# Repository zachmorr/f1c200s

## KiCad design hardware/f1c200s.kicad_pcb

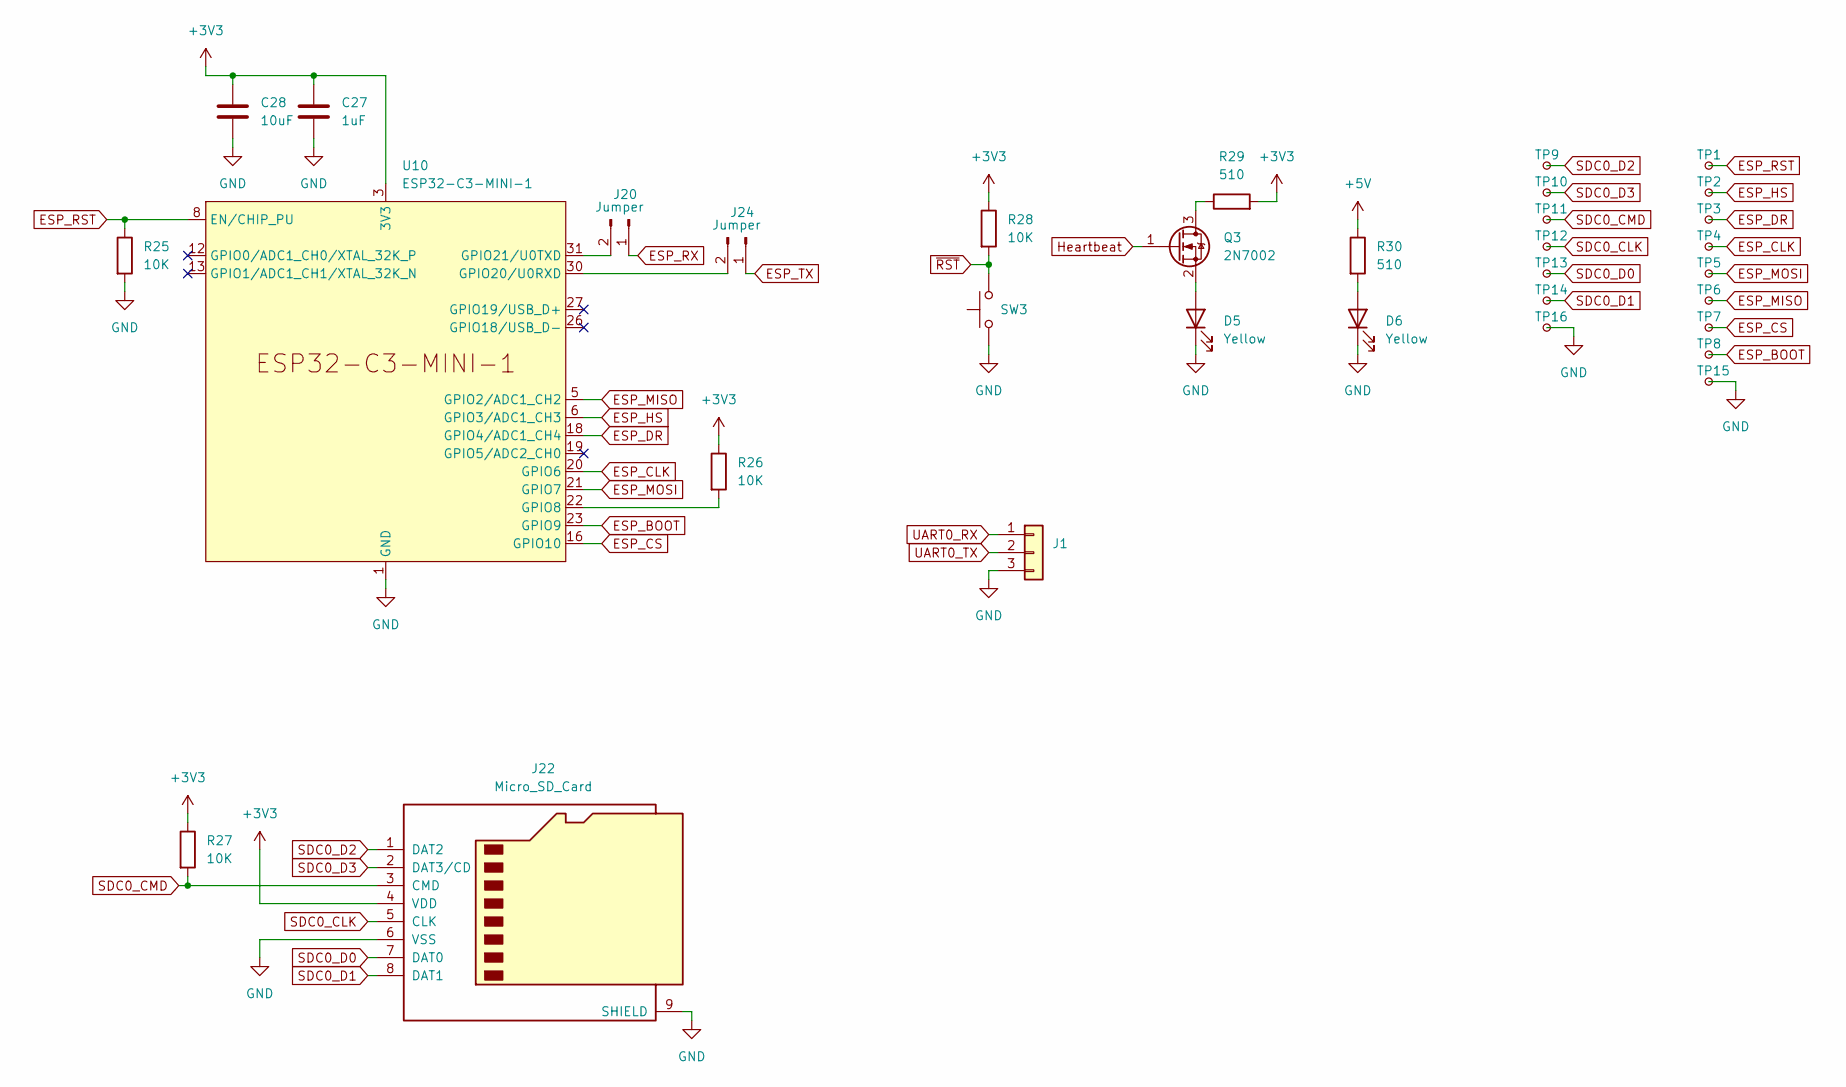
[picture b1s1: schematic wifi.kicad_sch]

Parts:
C27: 1uF; C_0402_1005Metric; LCSC C52923
C28: 10uF; C_0402_1005Metric; LCSC C15525
D5, D6: Yellow; LED_0603_1608Metric; LCSC C72038
J1: Conn_01x03; PinHeader_1x03_P2.54mm_Vertical
J20, J24: Jumper; PinHeader_1x02_P2.54mm_Vertical
J22: Micro_SD_Card; microSD_HC_Molex_104031-0811; LCSC C585350
Q3: 2N7002; SOT-23; LCSC C8545
R25, R26, R27, R28: 10K; R_0603_1608Metric; LCSC C25804
R29, R30: 510; R_0603_1608Metric; LCSC C23193
SW3: SW_Push; SW_Push_1P1T_XKB_TS-1187A; LCSC C318884
TP1, TP2, TP3, TP4, TP5, TP6, TP7, TP8, TP9, TP10, TP11, TP12, TP13, TP14, TP15, TP16: TestPoint_Small; TestPoint_Pad_D1.0mm
U10: ESP32-C3-MINI-1

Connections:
+3V3: C27.1, C28.1, J22.4 (VDD), R26.1, R27.1, R28.1, R29.2, U10.3 (3V3); also elsewhere on the board
+5V: R30.1; also elsewhere on the board
ESP_BOOT: TP8.1, U10.23 (GPIO9); also elsewhere on the board
ESP_CLK: TP4.1, U10.20 (GPIO6); also elsewhere on the board
ESP_CS: TP7.1, U10.16 (GPIO10); also elsewhere on the board
ESP_DR: TP3.1, U10.18 (GPIO4/ADC1_CH4); also elsewhere on the board
ESP_HS: TP2.1, U10.6 (GPIO3/ADC1_CH3); also elsewhere on the board
ESP_MISO: TP6.1, U10.5 (GPIO2/ADC1_CH2); also elsewhere on the board
ESP_MOSI: TP5.1, U10.21 (GPIO7); also elsewhere on the board
ESP_RST: R25.1, TP1.1, U10.8 (EN/CHIP_PU); also elsewhere on the board
ESP_RX: J20.1; also elsewhere on the board
ESP_TX: J24.1; also elsewhere on the board
GND: C27.2, C28.2, D5.1 (K), D6.1 (K), J1.3, J22.6 (VSS), J22.9 (SHIELD), R25.2, SW3.1, TP15.1, TP16.1, U10.1 (GND), U10.2 (GND), U10.11 (GND), U10.14 (GND), U10.36 (GND), U10.37 (GND), U10.38 (GND), U10.39 (GND), U10.40 (GND), U10.41 (GND), U10.42 (GND), U10.43 (GND), U10.44 (GND), U10.45 (GND), U10.46 (GND), U10.47 (GND), U10.48 (GND), U10.49 (GND), U10.50 (GND), U10.51 (GND), U10.52 (GND), U10.53 (GND); also elsewhere on the board
Heartbeat: Q3.1 (G)
unnamed: D5.2 (A), Q3.2 (S)
unnamed: D6.2 (A), R30.2
unnamed: J20.2, U10.31 (GPIO21/U0TXD)
unnamed: J24.2, U10.30 (GPIO20/U0RXD)
unnamed: Q3.3 (D), R29.1
unnamed: R26.2, U10.22 (GPIO8)
SDC0_CLK: J22.5 (CLK), TP12.1; also elsewhere on the board
SDC0_CMD: J22.3 (CMD), R27.2, TP11.1; also elsewhere on the board
SDC0_D0: J22.7 (DAT0), TP13.1; also elsewhere on the board
SDC0_D1: J22.8 (DAT1), TP14.1; also elsewhere on the board
SDC0_D2: J22.1 (DAT2), TP9.1; also elsewhere on the board
SDC0_D3: J22.2 (DAT3/CD), TP10.1; also elsewhere on the board
UART0_RX: J1.1; also elsewhere on the board
UART0_TX: J1.2; also elsewhere on the board
~RST: R28.2, SW3.2; also elsewhere on the board

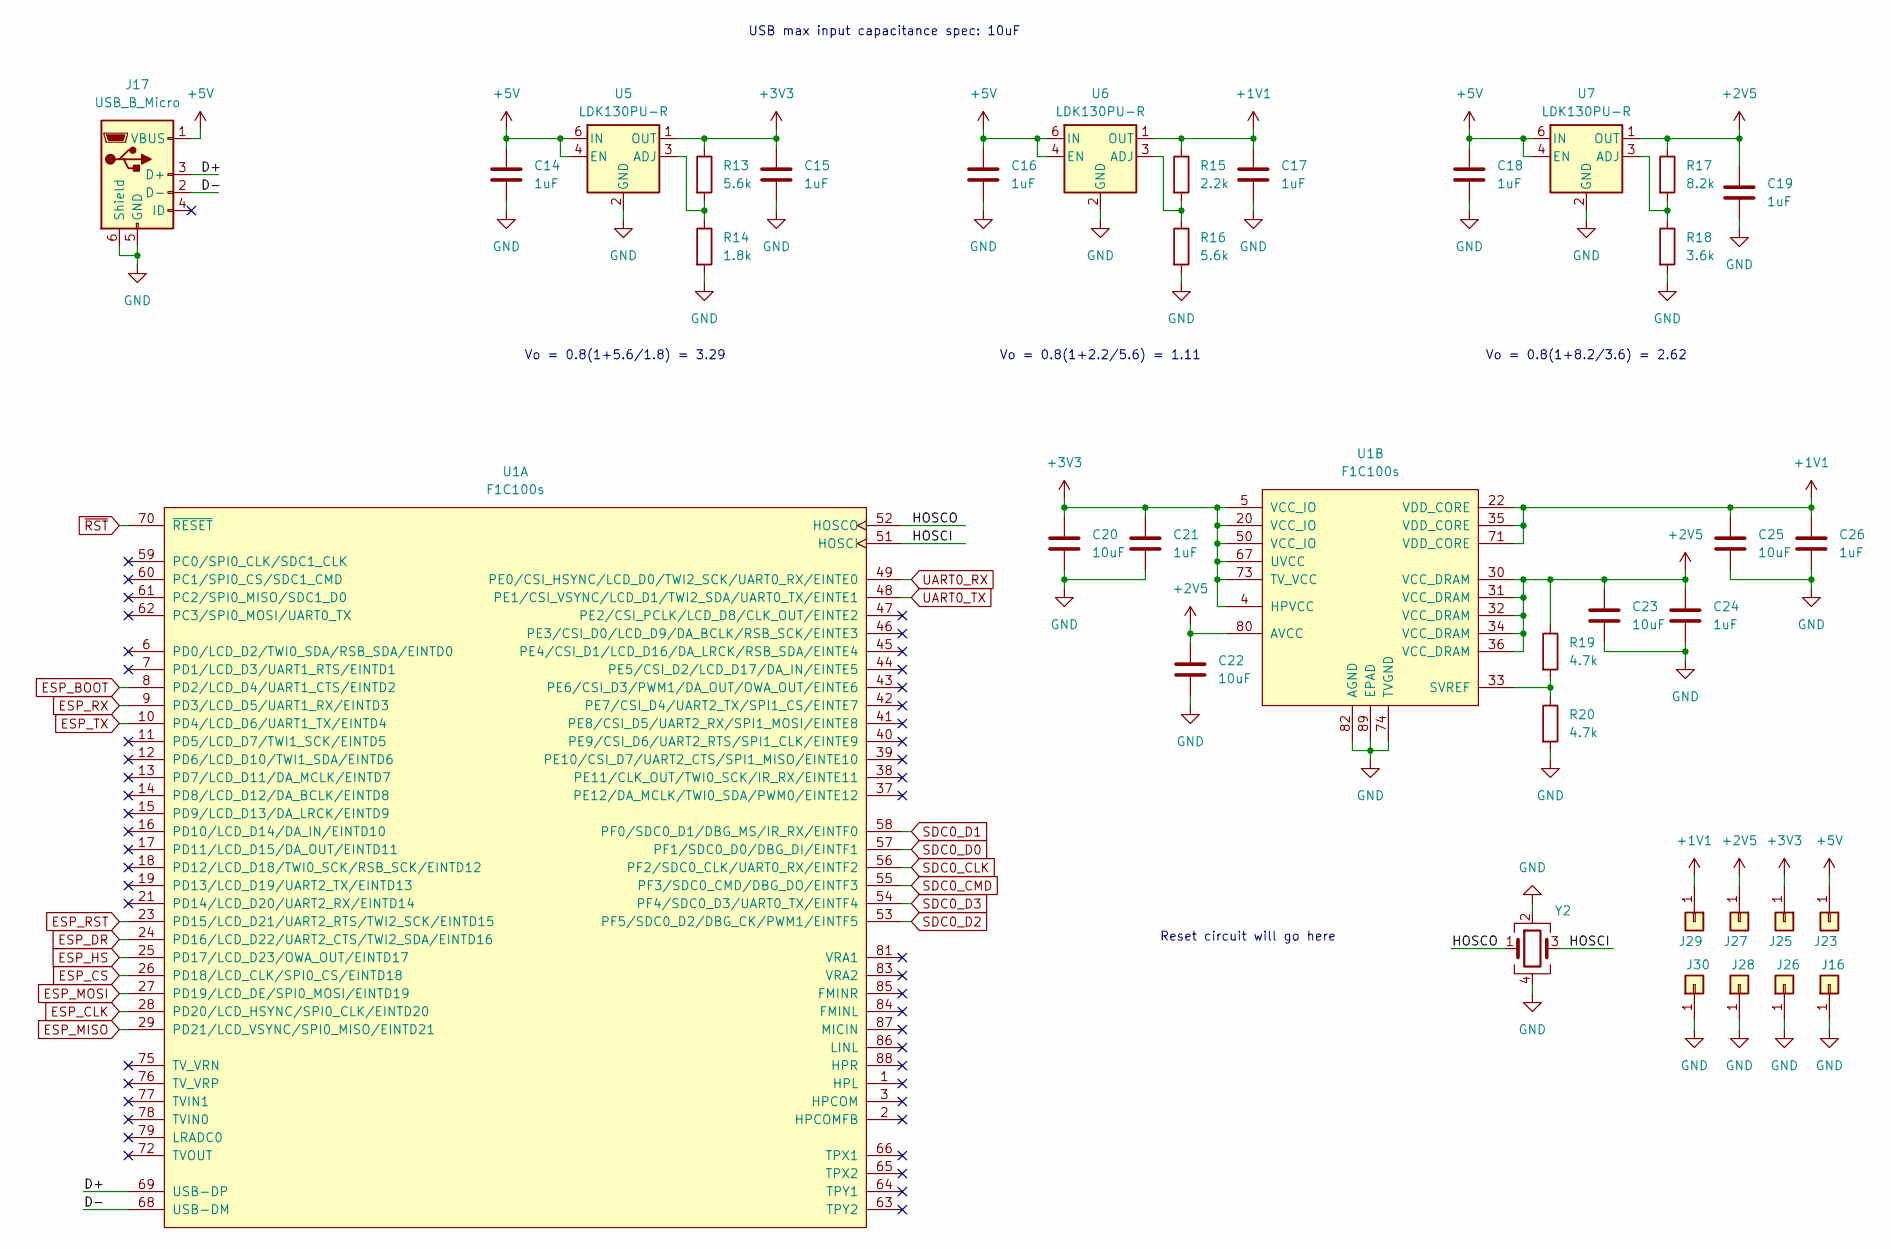
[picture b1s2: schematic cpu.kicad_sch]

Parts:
C14, C15, C16, C17, C18, C19, C21, C24, C26: 1uF; C_0402_1005Metric; LCSC C52923
C20, C22, C23, C25: 10uF; C_0402_1005Metric; LCSC C15525
J16, J23, J25, J26, J27, J28, J29, J30: Conn_01x01; PinHeader_1x01_P2.54mm_Vertical
J17: USB_B_Micro; USB_Micro-B_Amphenol_10118193-0001LF_Horizontal; LCSC C132562
R13, R16: 5.6k; R_0603_1608Metric; LCSC C23189
R14: 1.8k; R_0603_1608Metric; LCSC C4177
R15: 2.2k; R_0603_1608Metric; LCSC C4190
R17: 8.2k; R_0603_1608Metric; LCSC C25981
R18: 3.6k; R_0603_1608Metric; LCSC C22980
R19, R20: 4.7k; R_0402_1005Metric; LCSC C25900
U1: F1C100s; QFN-88_EP_10x10_Pitch0.4mm
U5, U6, U7: LDK130PU-R; DFN-6_1.3x1.2mm_P0.4mm; LCSC C157446
Y2: XRCGB24M000F0G00R0; Crystal_SMD_2016-4Pin_2.0x1.6mm; LCSC C524653

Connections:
+1V1: C17.1, C25.1, C26.1, J29.1, R15.1, U1.22 (VDD_CORE), U1.35 (VDD_CORE), U1.71 (VDD_CORE), U6.1 (OUT)
+2V5: C19.1, C22.1, C23.1, C24.1, J27.1, R17.1, R19.1, U1.30 (VCC_DRAM), U1.31 (VCC_DRAM), U1.32 (VCC_DRAM), U1.34 (VCC_DRAM), U1.36 (VCC_DRAM), U1.80 (AVCC), U7.1 (OUT)
+3V3: C15.1, C20.1, C21.1, J25.1, R13.1, U1.4 (HPVCC), U1.5 (VCC_IO), U1.20 (VCC_IO), U1.50 (VCC_IO), U1.67 (UVCC), U1.73 (TV_VCC), U5.1 (OUT); also elsewhere on the board
+5V: C14.1, C16.1, C18.1, J17.1 (VBUS), J23.1, U5.4 (EN), U5.6 (IN), U6.4 (EN), U6.6 (IN), U7.4 (EN), U7.6 (IN); also elsewhere on the board
/cpu/D+: J17.3 (D+), U1.69 (USB-DP)
/cpu/D-: J17.2 (D-), U1.68 (USB-DM)
/cpu/HOSCI: U1.51 (HOSCI), Y2.3
/cpu/HOSCO: U1.52 (HOSCO), Y2.1
ESP_BOOT: U1.8 (PD2/LCD_D4/UART1_CTS/EINTD2); also elsewhere on the board
ESP_CLK: U1.28 (PD20/LCD_HSYNC/SPI0_CLK/EINTD20); also elsewhere on the board
ESP_CS: U1.26 (PD18/LCD_CLK/SPI0_CS/EINTD18); also elsewhere on the board
ESP_DR: U1.24 (PD16/LCD_D22/UART2_CTS/TWI2_SDA/EINTD16); also elsewhere on the board
ESP_HS: U1.25 (PD17/LCD_D23/OWA_OUT/EINTD17); also elsewhere on the board
ESP_MISO: U1.29 (PD21/LCD_VSYNC/SPI0_MISO/EINTD21); also elsewhere on the board
ESP_MOSI: U1.27 (PD19/LCD_DE/SPI0_MOSI/EINTD19); also elsewhere on the board
ESP_RST: U1.23 (PD15/LCD_D21/UART2_RTS/TWI2_SCK/EINTD15); also elsewhere on the board
ESP_RX: U1.9 (PD3/LCD_D5/UART1_RX/EINTD3); also elsewhere on the board
ESP_TX: U1.10 (PD4/LCD_D6/UART1_TX/EINTD4); also elsewhere on the board
GND: C14.2, C15.2, C16.2, C17.2, C18.2, C19.2, C20.2, C21.2, C22.2, C23.2, C24.2, C25.2, C26.2, J16.1, J17.5 (GND), J17.6 (Shield), J26.1, J28.1, J30.1, R14.2, R16.2, R18.2, R20.2, U1.74 (TVGND), U1.82 (AGND), U1.89 (EPAD), U5.2 (GND), U6.2 (GND), U7.2 (GND), Y2.2, Y2.4; also elsewhere on the board
unnamed: R19.2, R20.1, U1.33 (SVREF)
unnamed: R13.2, R14.1, U5.3 (ADJ)
unnamed: R15.2, R16.1, U6.3 (ADJ)
unnamed: R17.2, R18.1, U7.3 (ADJ)
SDC0_CLK: U1.56 (PF2/SDC0_CLK/UART0_RX/EINTF2); also elsewhere on the board
SDC0_CMD: U1.55 (PF3/SDC0_CMD/DBG_DO/EINTF3); also elsewhere on the board
SDC0_D0: U1.57 (PF1/SDC0_D0/DBG_DI/EINTF1); also elsewhere on the board
SDC0_D1: U1.58 (PF0/SDC0_D1/DBG_MS/IR_RX/EINTF0); also elsewhere on the board
SDC0_D2: U1.53 (PF5/SDC0_D2/DBG_CK/PWM1/EINTF5); also elsewhere on the board
SDC0_D3: U1.54 (PF4/SDC0_D3/UART0_TX/EINTF4); also elsewhere on the board
UART0_RX: U1.49 (PE0/CSI_HSYNC/LCD_D0/TWI2_SCK/UART0_RX/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); also elsewhere on the board
UART0_TX: U1.48 (PE1/CSI_VSYNC/LCD_D1/TWI2_SDA/UART0_TX/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); also elsewhere on the board
~RST: U1.70 (~RESET); also elsewhere on the board

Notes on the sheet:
Vo = 0.8(1+2.2/5.6) = 1.11
Vo = 0.8(1+5.6/1.8) = 3.29
Vo = 0.8(1+8.2/3.6) = 2.62
USB max input capacitance spec: 10uF
Reset circuit will go here

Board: 4 copper layers, 68 parts (0 on the bottom side), 38 nets, no tracks yet.

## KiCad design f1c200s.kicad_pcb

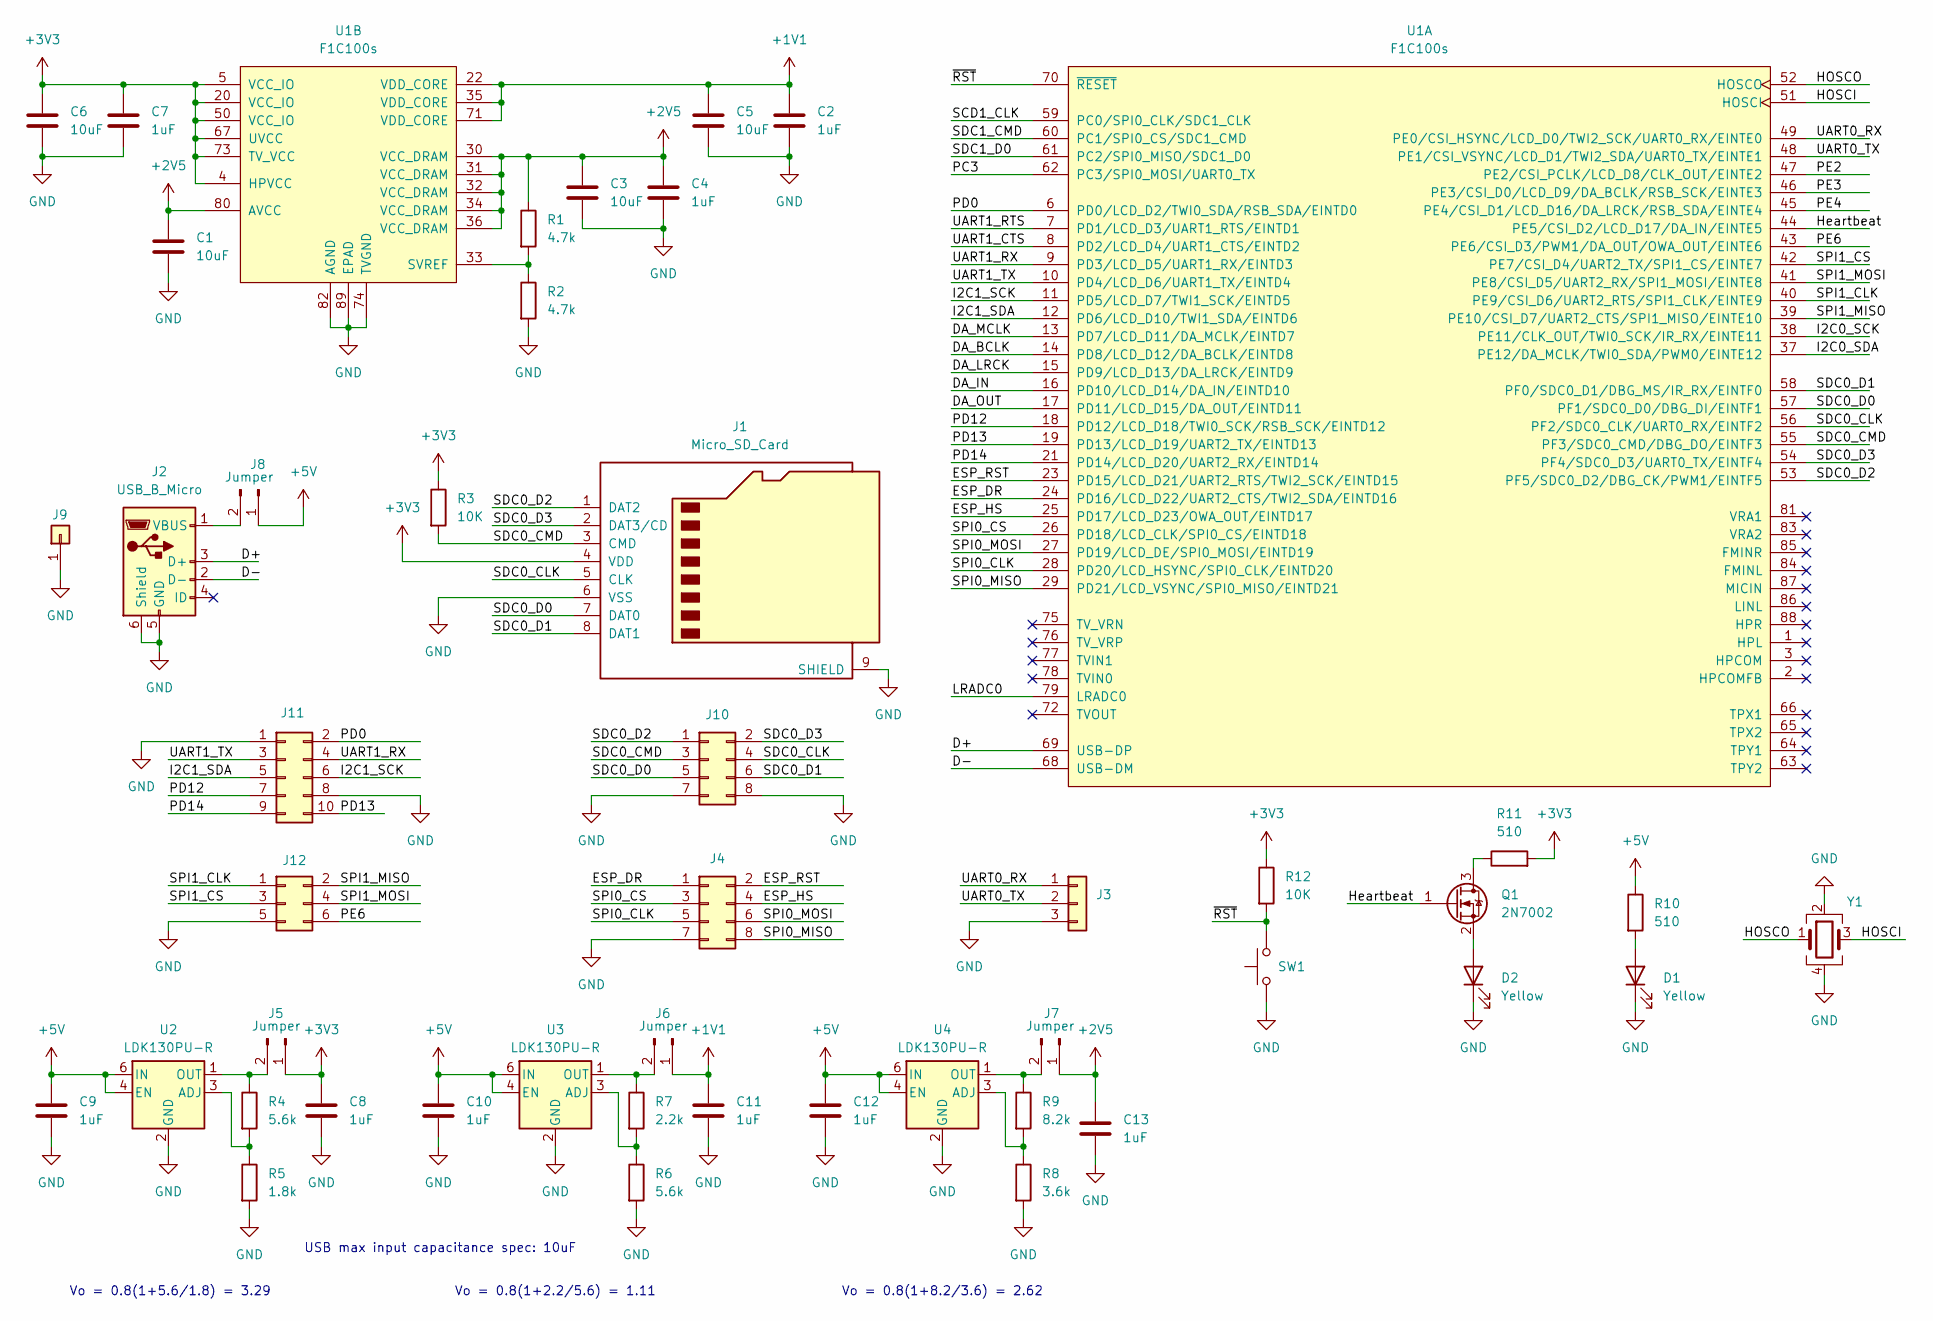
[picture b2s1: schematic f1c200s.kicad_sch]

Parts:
C1, C3, C5, C6: 10uF; C_0402_1005Metric; LCSC C15525
C2, C4, C7, C8, C9, C10, C11, C12, C13: 1uF; C_0402_1005Metric; LCSC C52923
D1, D2: Yellow; LED_0603_1608Metric; LCSC C72038
J1: Micro_SD_Card; microSD_HC_Molex_104031-0811; LCSC C585350
J2: USB_B_Micro; USB_Micro-B_Amphenol_10118193-0001LF_Horizontal; LCSC C132562
J3: Conn_01x03; PinHeader_1x03_P2.54mm_Vertical
J4, J10: Conn_01x07; PinHeader_2x04_P2.54mm_Vertical
J5, J6, J7, J8: Jumper; PinHeader_1x02_P2.54mm_Vertical
J9: Conn_01x01; PinHeader_1x01_P2.54mm_Vertical
J11: Conn_02x05_Odd_Even; PinHeader_2x05_P2.54mm_Vertical
J12: Conn_02x03_Odd_Even; PinHeader_2x03_P2.54mm_Vertical
Q1: 2N7002; SOT-23; LCSC C8545
R1, R2: 4.7k; R_0402_1005Metric; LCSC C25900
R3, R12: 10K; R_0603_1608Metric; LCSC C25804
R4, R6: 5.6k; R_0603_1608Metric; LCSC C23189
R5: 1.8k; R_0603_1608Metric; LCSC C4177
R7: 2.2k; R_0603_1608Metric; LCSC C4190
R8: 3.6k; R_0603_1608Metric; LCSC C22980
R9: 8.2k; R_0603_1608Metric; LCSC C25981
R10, R11: 510; R_0603_1608Metric; LCSC C23193
SW1: SW_Push; SW_Push_1P1T_XKB_TS-1187A; LCSC C318884
U1: F1C100s; QFN-88_EP_10x10_Pitch0.4mm; LCSC C2879851
U2, U3, U4: LDK130PU-R; DFN-6_1.3x1.2mm_P0.4mm; LCSC C157446
Y1: XRCGB24M000F0G00R0; Crystal_SMD_2016-4Pin_2.0x1.6mm; LCSC C524653

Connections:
+1V1: C2.1, C5.1, C11.1, J6.1, U1.22 (VDD_CORE), U1.35 (VDD_CORE), U1.71 (VDD_CORE)
+2V5: C1.1, C3.1, C4.1, C13.1, J7.1, R1.1, U1.30 (VCC_DRAM), U1.31 (VCC_DRAM), U1.32 (VCC_DRAM), U1.34 (VCC_DRAM), U1.36 (VCC_DRAM), U1.80 (AVCC)
+3V3: C6.1, C7.1, C8.1, J1.4 (VDD), J5.1, R3.1, R11.2, R12.1, U1.4 (HPVCC), U1.5 (VCC_IO), U1.20 (VCC_IO), U1.50 (VCC_IO), U1.67 (UVCC), U1.73 (TV_VCC)
+5V: C9.1, C10.1, C12.1, J8.1, R10.1, U2.4 (EN), U2.6 (IN), U3.4 (EN), U3.6 (IN), U4.4 (EN), U4.6 (IN)
/D+: J2.3 (D+), U1.69 (USB-DP)
/D-: J2.2 (D-), U1.68 (USB-DM)
/DA_BCLK: U1.14 (PD8/LCD_D12/DA_BCLK/EINTD8)
/DA_IN: U1.16 (PD10/LCD_D14/DA_IN/EINTD10)
/DA_LRCK: U1.15 (PD9/LCD_D13/DA_LRCK/EINTD9)
/DA_MCLK: U1.13 (PD7/LCD_D11/DA_MCLK/EINTD7)
/DA_OUT: U1.17 (PD11/LCD_D15/DA_OUT/EINTD11)
/ESP_DR: J4.1, U1.24 (PD16/LCD_D22/UART2_CTS/TWI2_SDA/EINTD16)
/ESP_HS: J4.4, U1.25 (PD17/LCD_D23/OWA_OUT/EINTD17)
/ESP_RST: J4.2, U1.23 (PD15/LCD_D21/UART2_RTS/TWI2_SCK/EINTD15)
/HOSCI: U1.51 (HOSCI), Y1.3
/HOSCO: U1.52 (HOSCO), Y1.1
/Heartbeat: Q1.1 (G), U1.44 (PE5/CSI_D2/LCD_D17/DA_IN/EINTE5)
/I2C0_SCK: U1.38 (PE11/CLK_OUT/TWI0_SCK/IR_RX/EINTE11)
/I2C0_SDA: U1.37 (PE12/DA_MCLK/TWI0_SDA/PWM0/EINTE12)
/I2C1_SCK: J11.6, U1.11 (PD5/LCD_D7/TWI1_SCK/EINTD5)
/I2C1_SDA: J11.5, U1.12 (PD6/LCD_D10/TWI1_SDA/EINTD6)
/LRADC0: U1.79 (LRADC0)
/PC3: U1.62 (PC3/SPI0_MOSI/UART0_TX)
/PD0: J11.2, U1.6 (PD0/LCD_D2/TWI0_SDA/RSB_SDA/EINTD0)
/PD12: J11.7, U1.18 (PD12/LCD_D18/TWI0_SCK/RSB_SCK/EINTD12)
/PD13: J11.10, U1.19 (PD13/LCD_D19/UART2_TX/EINTD13)
/PD14: J11.9, U1.21 (PD14/LCD_D20/UART2_RX/EINTD14)
/PE2: U1.47 (PE2/CSI_PCLK/LCD_D8/CLK_OUT/EINTE2)
/PE3: U1.46 (PE3/CSI_D0/LCD_D9/DA_BCLK/RSB_SCK/EINTE3)
/PE4: U1.45 (PE4/CSI_D1/LCD_D16/DA_LRCK/RSB_SDA/EINT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)
/PE6: J12.6, U1.43 (PE6/CSI_D3/PWM1/DA_OUT/OWA_OUT/EINTE6)
/SCD1_CLK: U1.59 (PC0/SPI0_CLK/SDC1_CLK)
/SDC0_CLK: J1.5 (CLK), J10.4, U1.56 (PF2/SDC0_CLK/UART0_RX/EINTF2)
/SDC0_CMD: J1.3 (CMD), J10.3, R3.2, U1.55 (PF3/SDC0_CMD/DBG_DO/EINTF3)
/SDC0_D0: J1.7 (DAT0), J10.5, U1.57 (PF1/SDC0_D0/DBG_DI/EINTF1)
/SDC0_D1: J1.8 (DAT1), J10.6, U1.58 (PF0/SDC0_D1/DBG_MS/IR_RX/EINTF0)
/SDC0_D2: J1.1 (DAT2), J10.1, U1.53 (PF5/SDC0_D2/DBG_CK/PWM1/EINTF5)
/SDC0_D3: J1.2 (DAT3/CD), J10.2, U1.54 (PF4/SDC0_D3/UART0_TX/EINTF4)
/SDC1_CMD: U1.60 (PC1/SPI0_CS/SDC1_CMD)
/SDC1_D0: U1.61 (PC2/SPI0_MISO/SDC1_D0)
/SPI0_CLK: J4.5, U1.28 (PD20/LCD_HSYNC/SPI0_CLK/EINTD20)
/SPI0_CS: J4.3, U1.26 (PD18/LCD_CLK/SPI0_CS/EINTD18)
/SPI0_MISO: J4.8, U1.29 (PD21/LCD_VSYNC/SPI0_MISO/EINTD21)
/SPI0_MOSI: J4.6, U1.27 (PD19/LCD_DE/SPI0_MOSI/EINTD19)
/SPI1_CLK: J12.1, U1.40 (PE9/CSI_D6/UART2_RTS/SPI1_CLK/EINTE9)
/SPI1_CS: J12.3, U1.42 (PE7/CSI_D4/UART2_TX/SPI1_CS/EINTE7)
/SPI1_MISO: J12.2, U1.39 (PE10/CSI_D7/UART2_CTS/SPI1_MISO/EINTE10)
/SPI1_MOSI: J12.4, U1.41 (PE8/CSI_D5/UART2_RX/SPI1_MOSI/EINTE8)
/UART0_RX: J3.1, U1.49 (PE0/CSI_HSYNC/LCD_D0/TWI2_SCK/UART0_RX/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)
/UART0_TX: J3.2, U1.48 (PE1/CSI_VSYNC/LCD_D1/TWI2_SDA/UART0_TX/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)
/UART1_CTS: U1.8 (PD2/LCD_D4/UART1_CTS/EINTD2)
/UART1_RTS: U1.7 (PD1/LCD_D3/UART1_RTS/EINTD1)
/UART1_RX: J11.4, U1.9 (PD3/LCD_D5/UART1_RX/EINTD3)
/UART1_TX: J11.3, U1.10 (PD4/LCD_D6/UART1_TX/EINTD4)
/~RST: R12.2, SW1.2, U1.70 (~RESET)
GND: C1.2, C2.2, C3.2, C4.2, C5.2, C6.2, C7.2, C8.2, C9.2, C10.2, C11.2, C12.2, C13.2, D1.1 (K), D2.1 (K), J1.6 (VSS), J1.9 (SHIELD), J2.5 (GND), J2.6 (Shield), J3.3, J4.7, J9.1, J10.7, J10.8, J11.1, J11.8, J12.5, R2.2, R5.2, R6.2, R8.2, SW1.1, U1.74 (TVGND), U1.82 (AGND), U1.89 (EPAD), U2.2 (GND), U3.2 (GND), U4.2 (GND), Y1.2, Y1.4
unnamed: D1.2 (A), R10.2
unnamed: D2.2 (A), Q1.2 (S)
unnamed: J2.1 (VBUS), J8.2
unnamed: J5.2, R4.1, U2.1 (OUT)
unnamed: J6.2, R7.1, U3.1 (OUT)
unnamed: J7.2, R9.1, U4.1 (OUT)
unnamed: Q1.3 (D), R11.1
unnamed: R1.2, R2.1, U1.33 (SVREF)
unnamed: R4.2, R5.1, U2.3 (ADJ)
unnamed: R6.1, R7.2, U3.3 (ADJ)
unnamed: R8.1, R9.2, U4.3 (ADJ)

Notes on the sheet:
Vo = 0.8(1+2.2/5.6) = 1.11
USB max input capacitance spec: 10uF
Vo = 0.8(1+5.6/1.8) = 3.29
Vo = 0.8(1+8.2/3.6) = 2.62

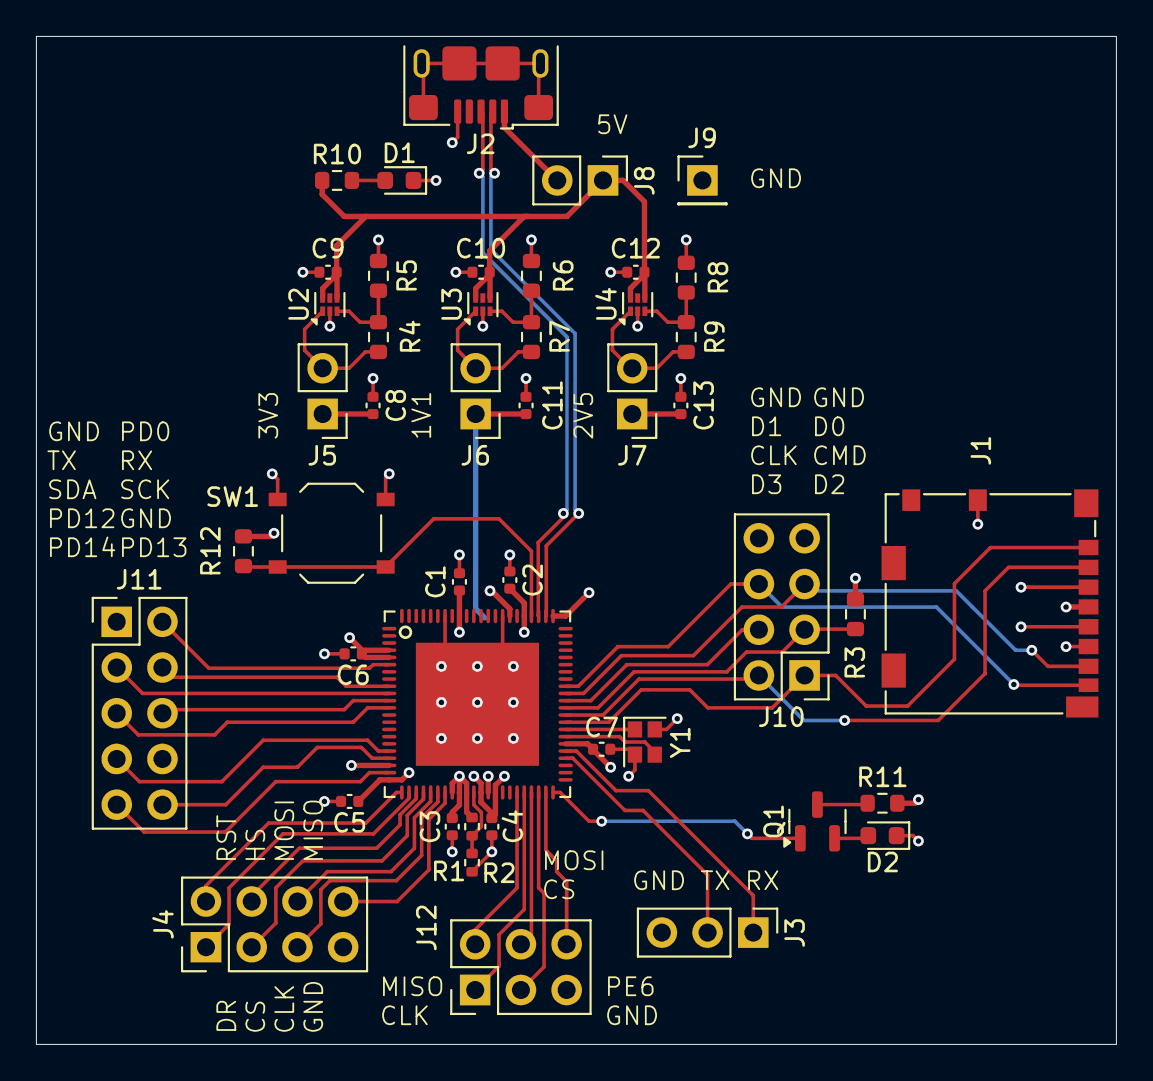
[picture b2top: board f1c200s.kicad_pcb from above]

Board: 4 copper layers, 60.0 x 56.0 mm, 46 parts (0 on the bottom side), 50 nets.

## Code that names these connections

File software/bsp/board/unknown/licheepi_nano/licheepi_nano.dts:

// SPDX-License-Identifier: (GPL-2.0+ OR X11)
/*
 * Copyright 2018 Icenowy Zheng <icenowy@aosc.io>
 */

/dts-v1/;
#include "allwinner/suniv-f1c100s.dtsi"

#include <dt-bindings/gpio/gpio.h>

/ {
	model = "Lichee Pi Nano";
	compatible = "licheepi,licheepi-nano", "allwinner,suniv-f1c100s";

	aliases {
		mmc0 = &mmc0;
		serial0 = &uart0;
		spi0 = &spi0;
		spi1 = &spi1;
		pio = &pio;
	};

	chosen {
		stdout-path = "serial0:115200n8";
	};

	reg_vcc3v3: vcc3v3 {
		compatible = "regulator-fixed";
		regulator-name = "vcc3v3";
		regulator-min-microvolt = <3300000>;
		regulator-max-microvolt = <3300000>;
	};
};

&pio {
	spi0_pd_pins: spi0-pd-pins {
		pins = "PD20", "PD18", "PD21", "PD19";
		function = "spi0";
	};

	spi1_pe_pins: spi1-pe-pins {
		pins = "PE9", "PE7", "PE10", "PE8";
		function = "spi1";
	};
};

&mmc0 {
	broken-cd;
	bus-width = <4>;
	disable-wp;
	status = "okay";
	vmmc-supply = <&reg_vcc3v3>;
};

&spi0 {
	pinctrl-names = "default";
	pinctrl-0 = <&spi0_pd_pins>;
	status = "okay";
};

&spi1 {
	pinctrl-names = "default";
	pinctrl-0 = <&spi1_pe_pins>;
	status = "okay";

    spidev@0{
        compatible = "rohm,dh2228fv";
        reg = <0>;
        spi-max-frequency = <4000000>;
    };

};

&otg_sram {
	status = "okay";
};

&uart0 {
	pinctrl-names = "default";
	pinctrl-0 = <&uart0_pe_pins>;
	status = "okay";
};

&usb_otg {
	dr_mode = "otg";
	status = "okay";
};

&usbphy {
	usb0_id_det-gpios = <&pio 4 2 GPIO_ACTIVE_HIGH>; /* PE2 */
	status = "okay";
};

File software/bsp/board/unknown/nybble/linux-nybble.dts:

/dts-v1/;
#include "allwinner/suniv-f1c100s.dtsi"

#include <dt-bindings/gpio/gpio.h>

/ {
	model = "Nybble";
	compatible = "allwinner,suniv-f1c100s";

	aliases {
		mmc0 = &mmc0;
		serial0 = &uart0;
		serial2 = &uart2;
		spi0 = &spi0;
		pio = &pio;
	};

	chosen {
		stdout-path = "serial0:115200n8";
	};

	reg_vcc3v3: vcc3v3 {
		compatible = "regulator-fixed";
		regulator-name = "vcc3v3";
		regulator-min-microvolt = <3300000>;
		regulator-max-microvolt = <3300000>;
	};
};

&pio {
	spi0_pd_pins: spi0-pd-pins {
		pins = "PD20", "PD18", "PD21", "PD19";
		function = "spi0";
	};


	uart2_pd_pins: uart2-pd-pins {
		pins = "PD13", "PD14";
		function = "uart2";
	};
};

&mmc0 {
	broken-cd;
	bus-width = <4>;
	disable-wp;
	status = "okay";
	vmmc-supply = <&reg_vcc3v3>;
};

&spi0 {
	pinctrl-names = "default";
	pinctrl-0 = <&spi0_pd_pins>;
	status = "okay";
};

&otg_sram {
	status = "okay";
};

&uart0 {
	pinctrl-names = "default";
	pinctrl-0 = <&uart0_pe_pins>;
	status = "okay";
};

&uart2 {
	pinctrl-names = "default";
	pinctrl-0 = <&uart2_pd_pins>;
	status = "okay";
};

&usb_otg {
	dr_mode = "peripheral";
	status = "okay";
};

&usbphy {
	usb0_id_det-gpios = <&pio 4 2 GPIO_ACTIVE_HIGH>; /* PE2 */
	status = "okay";
};

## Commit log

2024-03-25 gitignore
2024-03-25 First version of dev board
2024-03-25 Adding project library tables
2024-04-03 Dev board V2
2024-04-14 Adding PDF
2024-07-07 restructure
2024-07-07 re-add bsp
2024-07-30 working
2024-08-12 working networking
2024-08-15 minimal working wifi setup
2024-08-29 renaming, adding user, removing root, working ssh
2024-09-01 Moving esp-hosted fork
2024-09-08 Adding 2nd uart + updating esp-hosted patch
2024-09-08 Adding schematic pdf
2024-10-19 Adding usb serial
2024-10-19 Adding documents
2024-10-19 Adding ESP32 to board, work in progress
2024-10-19 Updating sheet name
2024-11-24 Changing getty to gserial port
2024-12-01 Adding USB+adbd, removing NET
2024-12-10 Stable configuration
2024-12-10 updating defconfig
2024-12-15 Adding heartbeat and more utilities
